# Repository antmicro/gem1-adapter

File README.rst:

GEM1 Adapter
============

Copyright (c) 2020 `Antmicro <https://www.antmicro.com>`_

.. image:: https://img.shields.io/badge/View%20on-Antmicro%20Open%20Source%20Portal-332d37?style=flat-square
   :target: https://opensource.antmicro.com/projects/gem1-adapter

.. figure:: img/zglue-gem1-adapter.jpg

This repository contains PCB design files for an adapter board accommodating the GEM1 chip created jointly by `zGlue <http://zglue.com>`_ and `Antmicro <http://www.antmicro.com>`_.
The `GEM1 design <https://zglue.com/design-automation/oci/project/gem1>`_ utilizes the zGlue ZiP chiplet technology and has been prepared using zGlue's `ChipBuilder <http://chipbuilder.zglue.com/>`_ tool.
The design has been produced as a single integrated circuit in the LGA-96 package.

The GEM1 chip contains the following components located on a dynamically reconfigurable interposer:

* 2x Lattice ``ICE40UP5K-UWG30ITR`` FPGAs used for processing and system control
* 32Mbit SPI FLASH memory
* 10-channel DPDT MIPI switch allowing to connect a 2-lane MIPI CSI-2 interface either to the processing FPGA or to external output (pass-through mode)
* 12MHz system clock generator 
* Internal LDOs and power management unit providing 1V2, 1V8, 2V5, 3V3 voltages

Power is supplied to the chip from a single ``VUSB`` voltage of 5 VDC.
The actual configuration of the system running inside the GEM1 zip depends on the configuration routing file that is uploaded to the ``Smart fabric`` interposer.
Also, pin functions of the LGA package may vary depending on the uploaded routing file.
The board break-routes signals for the MIPI CSI-2 interfaces (Input and Output), along with the internal flash and FPGA configuration interfaces, control signals and power supplies.

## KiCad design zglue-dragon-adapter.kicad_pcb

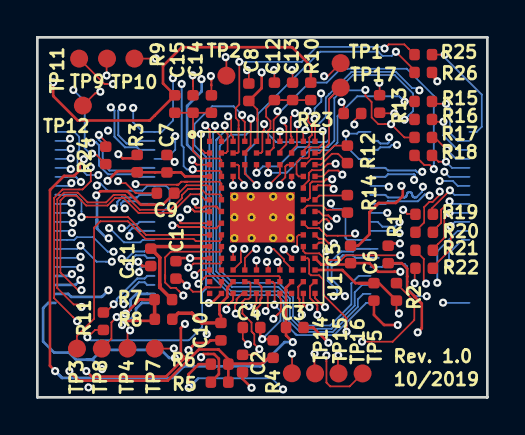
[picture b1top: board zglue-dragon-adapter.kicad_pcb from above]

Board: 6 copper layers, 25.0 x 20.0 mm, 59 parts (0 on the bottom side), 97 nets.

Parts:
C1: C_10u_0402; 0402-cap
C2, C3, C4: C_2u2_0402; 0402-cap
C5, C6, C7, C8, C9, C10, C11, C12, C14: C_100n_0402_6V3; 0402-cap
C13, C15: C_10n_0402; 0402-cap
J1, J2: 543630489
R1, R2, R3, R4, R5, R6, R7, R8, R15, R16, R17, R18, R19, R20, R21, R22, R25, R26: R_0R_0402; 0402-res
R9, R10, R12, R14, R23: R_100R_0402; 0402-res
R11: R_1k5_0402; 0402-res
R13: R_10k_0402; 0402-res
R24: R_220R_0402; 0402-res
TP1, TP2, TP3, TP4, TP5, TP7, TP8, TP9, TP10, TP11, TP12, TP14, TP15, TP16, TP17: TP_SMD1MM; Testpoint_smd_1mm
U1: zGlue-Dragon; Z-Glue_LGA-96

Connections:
/1V2: C4.1, R4.1, U1.N6
/1V2_SYS: J1.37, R4.2, R5.1, R6.1, R9.1, R10.1
/1V2_SYS_A: C9.1, R5.2, U1.E1
/1V2_SYS_B: C8.1, R6.2, U1.A5
/1V8: C2.1, R2.1, U1.N4
/1V8_SYS: C6.1, J1.38, R2.2, U1.M10
/2V5: C3.1, R3.1, U1.N8
/2V5_SYS: C7.1, J1.39, R3.2, U1.D1
/3V3: C1.1, R1.1, U1.L1
/3V3_SYS: C5.1, J1.40, R1.2, U1.B1, U1.L10, U1.N7
/CSI_CLK_FP_N: R23.2, U1.D10
/CSI_CLK_FP_P: R23.1, U1.D2
/CSI_CLK_IN_N: J1.3, U1.G1
/CSI_CLK_IN_P: J1.2, U1.G2
/CSI_CLK_OUT_N: J2.23, U1.F9
/CSI_CLK_OUT_P: J2.22, U1.E10
/CSI_D1_FP_N: R12.2, U1.C10
/CSI_D1_FP_P: R12.1, U1.C9
/CSI_D1_IN_N: J1.6, U1.H2
/CSI_D1_IN_P: J1.5, R24.2, U1.H1
/CSI_D1_OUT_N: J2.26, U1.H10
/CSI_D1_OUT_P: J2.25, U1.G10
/CSI_D2_FP_N: R14.2, U1.F10
/CSI_D2_FP_P: R14.1, U1.G9
/CSI_D2_IN_N: J1.9, U1.P4
/CSI_D2_IN_P: J1.8, U1.P3
/CSI_D2_OUT_N: J2.29, U1.K10
/CSI_D2_OUT_P: J2.28, U1.J10
/CSI_D3_IN_N: J1.12, U1.P5
/CSI_D3_IN_P: J1.11, U1.N5
/CSI_D3_OUT_N: J2.32, U1.P10
/CSI_D3_OUT_P: J2.31, U1.N10
/CSI_D4_IN_N: J1.15, U1.P6
/CSI_D4_IN_P: J1.14, U1.P7
/CSI_D4_OUT_N: J2.35, U1.P9
/CSI_D4_OUT_P: J2.34, U1.N9
/CSI_INT: R24.1, TP1.1, U1.C8
/CSI_OE: R13.1, U1.E9
/CTRL_OUT: J2.37, U1.B4
/CTRL_RST: R26.1, U1.C4
/CTRL_RST_FLASH_SOC_CS: J2.7, R26.2
/CTRL_SCK: R21.1, U1.E2
/CTRL_SI: R19.1, U1.F1
/CTRL_SO: R20.1, U1.F2
/CTRL_SS: R22.1, U1.C1
/DBG_RX: J1.26, U1.A8
/DBG_TX: J1.25, U1.B9
/DONE: J2.13, U1.B8
/EXTCLK_EN: TP7.1, U1.L3
/EXT_CLK: TP8.1, U1.K2
/E_CTRL_SCK: J2.10, R21.2
/E_CTRL_SI: J2.8, R19.2
/E_CTRL_SO: J2.9, R20.2
/E_CTRL_SS: J2.11, R22.2
/E_PROC_RST: J2.1, R25.2
/E_PROC_SCK: J2.4, R17.2
/E_PROC_SI: J2.2, R15.2
/E_PROC_SO: J2.3, R16.2
/E_PROC_SS: J2.5, R18.2
/I2C_0_SCL: J1.33, U1.J9
/I2C_0_SDA: J1.34, U1.H9
/I2C_1_SCL: J1.35, U1.A10
/I2C_1_SDA: J1.36, U1.A9
/LED1_ISINK: J1.29, TP14.1, U1.M5
/LED2_ISINK: J1.30, TP15.1, U1.M6
/LED3_ISINK: J1.31, TP16.1, U1.M7
/MIPI_SEL: TP2.1, U1.C7
/PC_RDY: TP4.1, U1.L2
/PIO1: TP11.1, U1.C3
/PIO2: TP10.1, U1.A3
/PIO3: TP9.1, U1.D9
/PROC_OUT_0: J2.38, U1.B2
/PROC_OUT_1: J2.39, U1.A2
/PROC_OUT_2: J2.40, U1.A1
/PROC_RST: R25.1, U1.B3
/PROC_SCK: R17.1, U1.C5
/PROC_SI: R15.1, U1.C6
/PROC_SO: R16.1, U1.B5
/PROC_SS: R18.1, U1.B6
/PWR_BTN: J1.28, U1.J1
/SYS_CLK: TP17.1, U1.B10
/TCK: J1.24, U1.K9
/TDI: J1.21, U1.L9
/TDO: J1.22, U1.L8
/TMS: J1.23, U1.M8
/ULPM_WAKE: TP12.1, U1.D3
/USB_DET: R11.1, U1.A4
/USB_D_N: J1.18, U1.A7
/USB_D_P: J1.17, R11.2, U1.B7
/VBATH: C11.1, R7.2, U1.K1
/VDDANA: C10.1, R8.2, U1.N3
/VPLL_A: C14.1, C15.1, R9.2, U1.C2
/VPLL_B: C12.1, C13.1, R10.2, U1.A6
/VSENSE: TP5.1, U1.M4
/VUSB: J1.19, J1.20, R7.1, R8.1
/ZIP_EN_L: TP3.1, U1.J2
GND: C1.2, C2.2, C3.2, C4.2, C5.2, C6.2, C7.2, C8.2, C9.2, C10.2, C11.2, C12.2, C13.2, C14.2, C15.2, J1.1, J1.4, J1.7, J1.10, J1.13, J1.16, J1.27, J1.32, J2.6, J2.12, J2.20, J2.21, J2.24, J2.27, J2.30, J2.33, J2.36, R13.2, U1.EP, U1.M1, U1.N2, U1.P2

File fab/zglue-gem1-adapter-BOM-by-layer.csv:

Reference,Quantity,Value,Footprint,Manufacturer,MPN,Layer,
TP1 TP10 TP11 TP12 TP14 TP15 TP16 TP17 TP2 TP3 TP4 TP5 TP7 TP8 TP9,15,TP_SMD1MM,Testpoint_smd_1mm,,,Virtual,
C1,1,C_10u_0402,0402-cap,TDK,C1005X5R0J106M050BC,Unknown,
C10 C11 C12 C14 C5 C6 C7 C8 C9,9,C_100n_0402_6V3,0402-cap,Walsin,0402X104K6R3CT,Unknown,
C13 C15,2,C_10n_0402,0402-cap,AVX,04025G103ZAT2A,Unknown,
C2 C3 C4,3,C_2u2_0402,0402-cap,TDK,C1005X5R1A225K050BC,Unknown,
J1 J2,2,543630489,543630489,Molex,543630489,Unknown,
R1 R15 R16 R17 R18 R19 R2 R20 R21 R22 R25 R26 R3 R4 R5 R6 R7 R8,18,R_0R_0402,0402-res,PANASONIC,ERJ2GE0R00X,Unknown,
R10 R12 R14 R23 R9,5,R_100R_0402,0402-res,BOURNS,CR0402-FX-1000GLF,Unknown,
R11,1,R_1k5_0402,0402-res,PANASONIC_ELECTRONIC_COMPONENTS,ERJ2RKF1501X,Unknown,
R13,1,R_10k_0402,0402-res,VISHAY,CRCW040210K0FKEDHP,Unknown,
R24,1,R_220R_0402,0402-res,TE_CONNECTIVITY_/_NEOHM,CRG0402J220R,Unknown,
U1,1,zGlue-GEM1,Z-Glue_LGA-96,zGlue/TSMC,GEM1,Unknown,

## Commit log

2019-10-02 Added README
2019-10-02 Added zGlue symbol library, added symbol to schematic
2019-10-02 Added MIPI termination
2019-10-02 Added .gitignore
2019-10-02 Added voltage filtering
2019-10-02 Added CSI signals
2019-10-02 Removed obsolete file
2020-02-19 Added b2b connectors
2020-02-19 Cleanup
2020-02-19 Tied LED signals to B2B connector, fixed CSI lane naming
2020-02-19 Added QSPI flash signals to unify with GEM2 adapter
2020-02-19 Added CSI INT
2020-02-19 Finished component placement
    Fixed G10 pad name on LGA-96 footprint
2020-02-19 QSPI signals marked as reserved
2020-02-19 Added NC to specified signals from ZiP
2020-02-19 Changed PCB stackup to 6-layer, added stackup table, changed design rules
2020-02-19 Routing finished
2020-02-19 Moved some capacitors and resistors away from LGA-96 chip
2020-02-19 Rotated PCB by 180 deg to match chip logo orientation
2020-02-19 Added LGA-96 STEP model
2020-02-19 Modified LGA-96 thermal pad on paste layer
2020-02-19 Design files used for PCB manufacturing
2020-02-19 Layout polishing, connected PROC_RST and CTRL_RST to chip via 0R
2020-02-19 Moved C1,2,3,4 closer to LDO output pins
2020-02-19 Added testpad for VSENSE
2020-02-19 Added second ground plane, updated gerbers
2020-02-19 Library cleanup
2020-02-19 Added PNG with marked impedance
2020-02-19 Updated naming convention, updated README
2020-02-19 Updated LGA-96 stencil pattern
2020-02-20 Updated directory structure
2020-02-27 README: minor fixes
2020-05-28 Review README
2020-10-01 Update photo
2020-10-01 Add OCI link
2021-05-01 Notes added by 'git notes add'
2022-05-27 Scale image
2022-05-27 Add badge
